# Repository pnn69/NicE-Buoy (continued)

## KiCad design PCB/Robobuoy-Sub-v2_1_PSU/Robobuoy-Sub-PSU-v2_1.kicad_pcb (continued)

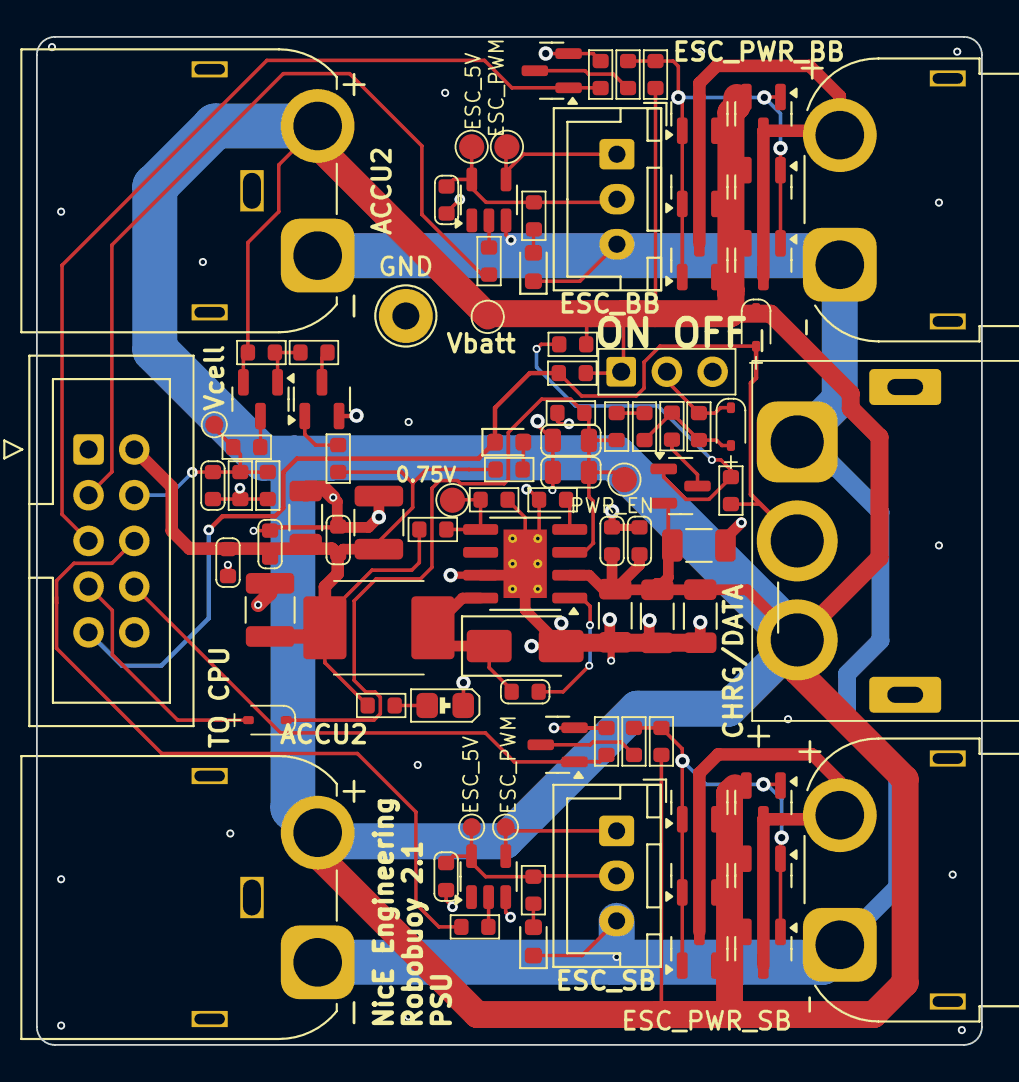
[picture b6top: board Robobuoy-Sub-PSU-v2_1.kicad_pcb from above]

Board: 4 copper layers, 52.5 x 56.0 mm, 94 parts (0 on the bottom side), 40 nets.

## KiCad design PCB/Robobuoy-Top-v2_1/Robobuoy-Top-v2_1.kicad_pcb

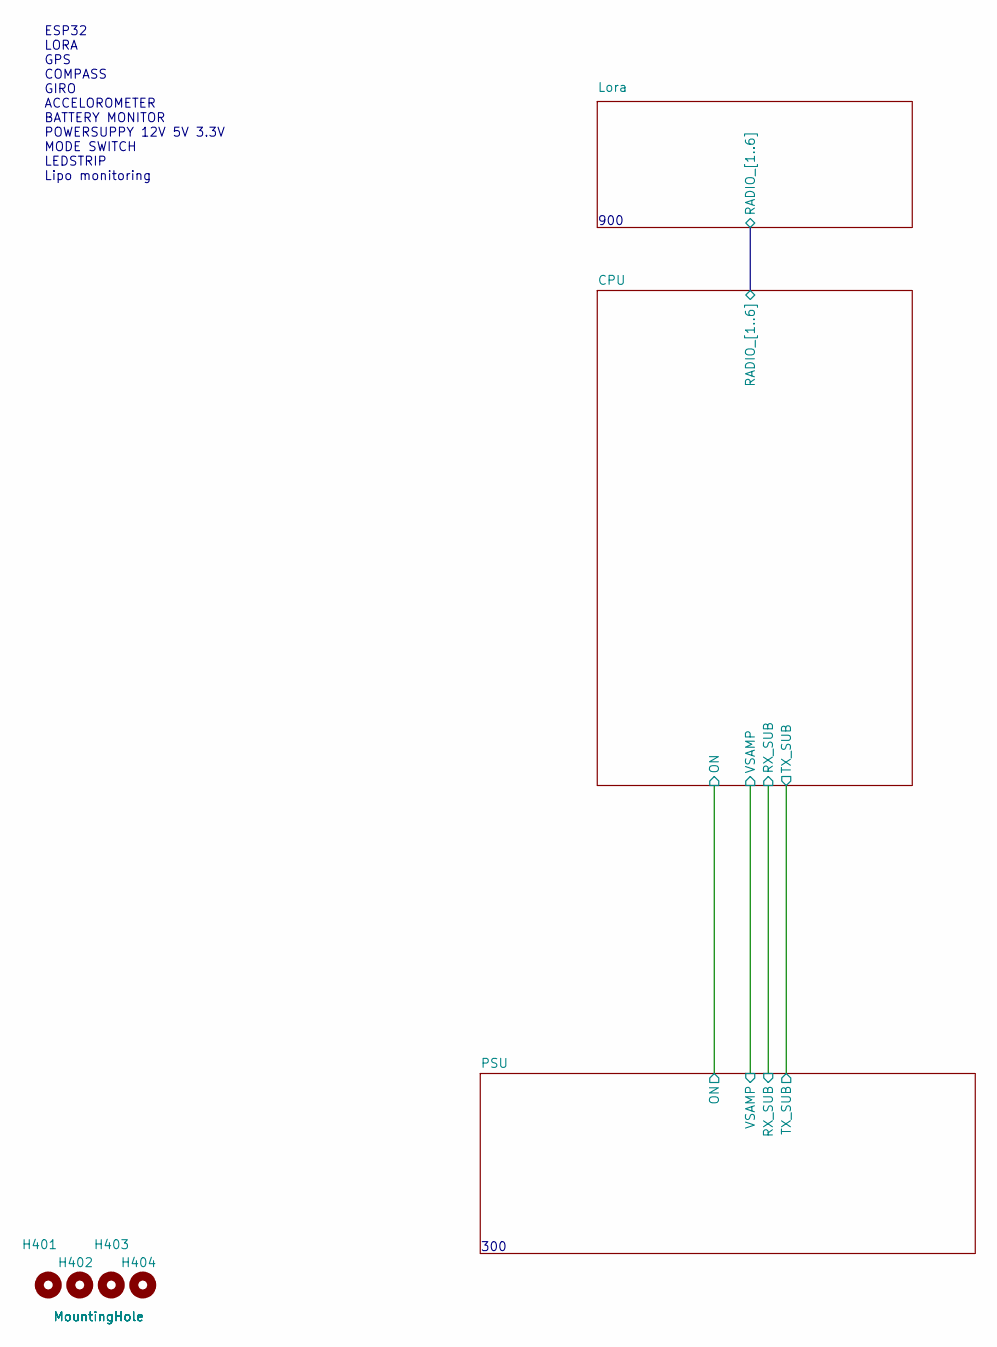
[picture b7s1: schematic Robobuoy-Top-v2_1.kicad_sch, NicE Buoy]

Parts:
H401, H402, H403, H404: MountingHole; NPTH_M3

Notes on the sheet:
300
ESP32 LORA GPS COMPASS GIRO ACCELOROMETER BATTERY MONITOR POWERSUPPY 12V 5V 3.3V MODE SWITCH LEDSTRIP Lipo monitoring
900

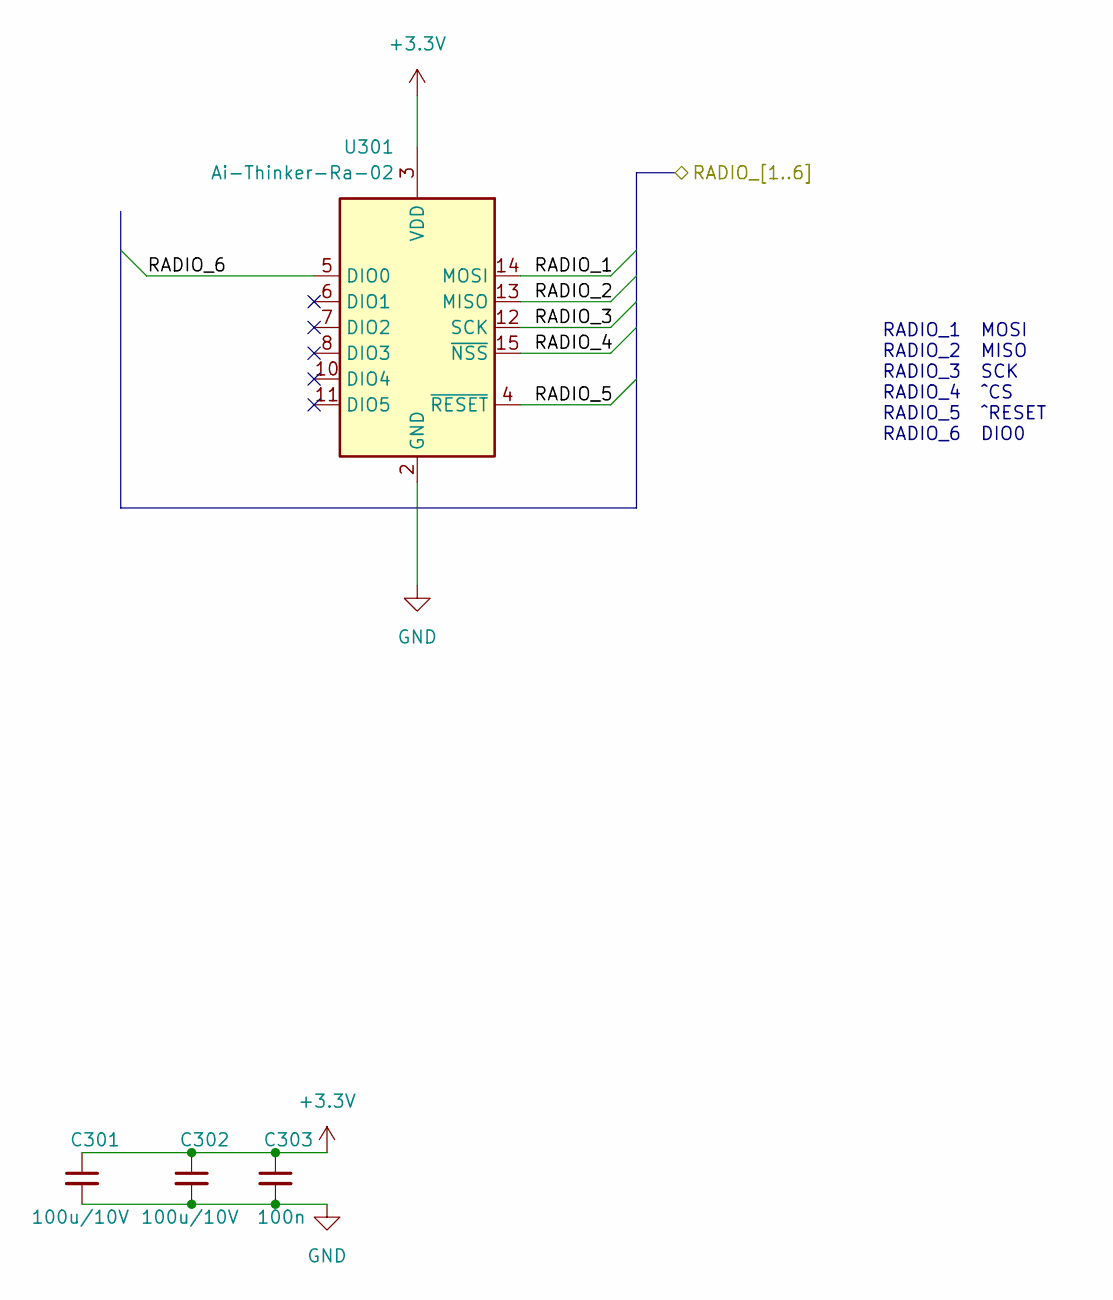
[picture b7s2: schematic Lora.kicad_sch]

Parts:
C301, C302: 100u/10V; C_1210_3225Metric; LCSC C23742
C303: 100n; C_0603; LCSC C14663
U301: Ai-Thinker-Ra-02; Ai-Thinker-Ra-02-LoRa; LCSC C90039

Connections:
+3.3V: C301.1, C302.1, C303.1, U301.3 (VDD); also elsewhere on the board
/CPU/RADIO_1: U301.14 (MOSI); also elsewhere on the board
/CPU/RADIO_2: U301.13 (MISO); also elsewhere on the board
/CPU/RADIO_3: U301.12 (SCK); also elsewhere on the board
/CPU/RADIO_4: U301.15 (~NSS); also elsewhere on the board
/CPU/RADIO_5: U301.4 (~RESET); also elsewhere on the board
/CPU/RADIO_6: U301.5 (DIO0); also elsewhere on the board
GND: C301.2, C302.2, C303.2, U301.1 (GND), U301.2 (GND), U301.9 (GND), U301.16 (GND); also elsewhere on the board

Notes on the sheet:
RADIO_1 MOSI RADIO_2 MISO RADIO_3 SCK RADIO_4 ^CS RADIO_5 ^RESET RADIO_6 DIO0

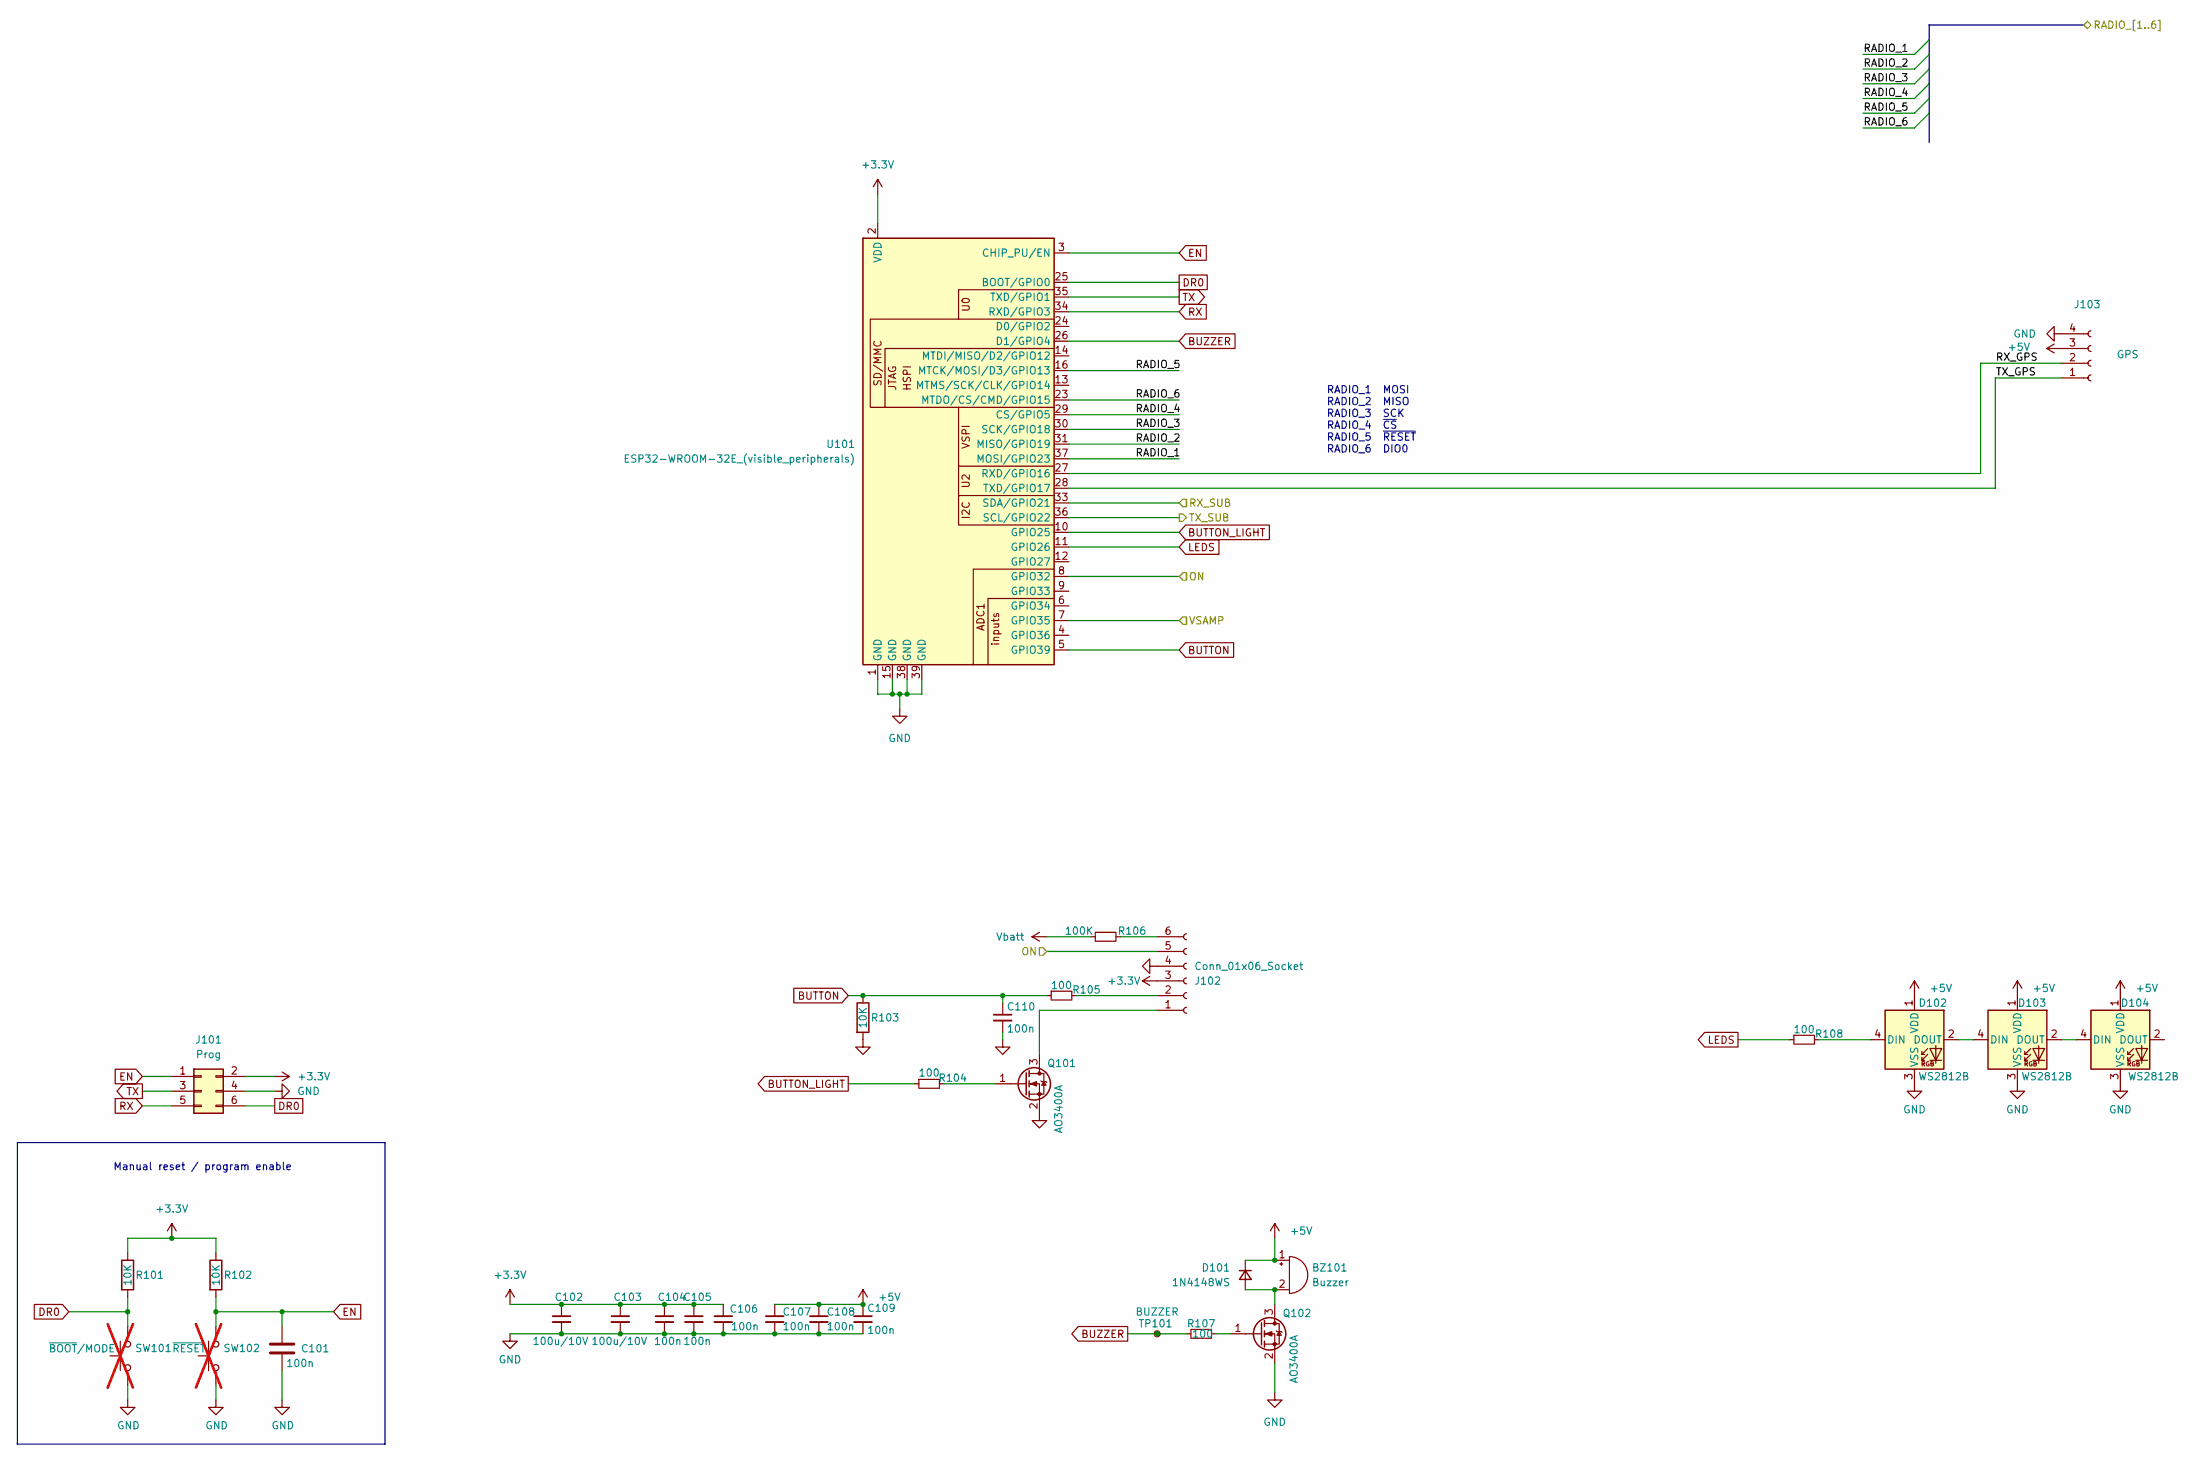
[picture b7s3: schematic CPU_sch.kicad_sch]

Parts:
BZ101: Buzzer; Buzzer-12x6.5x5.2; LCSC C968749
C101, C104, C105, C106, C107, C108, C109, C110: 100n; C_0603; LCSC C14663
C102, C103: 100u/10V; C_1210_3225Metric; LCSC C23742
D101: 1N4148WS; D_SOD-323_1.8x1.4x1.15; LCSC C2128
D102, D103, D104: WS2812B; LED_WS2812B_PLCC4_5.0x5.0mm_P3.2mm; LCSC C2843785
J101: Prog; IDC-Header_2x03_P2.54mm_Vertical; LCSC C11214
J102: Conn_01x06_Socket; JST_XH_B6B-XH-A_1x06_P2.50mm_Vertical; LCSC C5341205
J103: GPS; JST_XH_B4B-XH-A_1x04_P2.50mm_Vertical; LCSC C5341203
Q101, Q102: AO3400A; SOT-23; LCSC C20917
R101, R102, R103: 10K; R_0603; Farnell 2331736
R104, R105, R107, R108: 100; R_0603; LCSC C22775
R106: 100K; R_0603; LCSC C25804
SW101: ~{BOOT}/MODE; PinHeader_1x02_P2.54mm_Vertical; not fitted
SW102: ~{RESET}; PinHeader_1x02_P2.54mm_Vertical; not fitted
TP101: BUZZER; Testpad_1
U101: ESP32-WROOM-32E_(visible_peripherals); ESP32-WROOM-32; LCSC C82899

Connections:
+3.3V: C102.1, C103.1, C104.1, C105.1, C106.1, J101.2, J102.3, R101.1, R102.1, U101.2 (VDD); also elsewhere on the board
+5V: BZ101.1 (+), C107.1, C108.1, C109.1, D101.1 (K), D102.1 (VDD), D103.1 (VDD), D104.1 (VDD), J103.3; also elsewhere on the board
/CPU/ON: J102.5, U101.8 (GPIO32); also elsewhere on the board
/CPU/RADIO_1: U101.37 (MOSI/GPIO23); also elsewhere on the board
/CPU/RADIO_2: U101.31 (MISO/GPIO19); also elsewhere on the board
/CPU/RADIO_3: U101.30 (SCK/GPIO18); also elsewhere on the board
/CPU/RADIO_4: U101.29 (CS/GPIO5); also elsewhere on the board
/CPU/RADIO_5: U101.16 (MTCK/MOSI/D3/GPIO13); also elsewhere on the board
/CPU/RADIO_6: U101.23 (MTDO/CS/CMD/GPIO15); also elsewhere on the board
/CPU/RX_GPS: J103.2, U101.27 (RXD/GPIO16)
/CPU/RX_SUB: U101.33 (SDA/GPIO21); also elsewhere on the board
/CPU/TX_GPS: J103.1, U101.28 (TXD/GPIO17)
/CPU/TX_SUB: U101.36 (SCL/GPIO22); also elsewhere on the board
/CPU/VSAMP: U101.7 (GPIO35); also elsewhere on the board
BUTTON: C110.1, R103.1, R105.1, U101.5 (GPIO39)
BUTTON_LIGHT: R104.1, U101.10 (GPIO25)
BUZZER: R107.2, TP101.1, U101.26 (D1/GPIO4)
DR0: J101.6, R101.2, SW101.2, U101.25 (BOOT/GPIO0)
EN: C101.1, J101.1, R102.2, SW102.2, U101.3 (CHIP_PU/EN)
GND: C101.2, C102.2, C103.2, C104.2, C105.2, C106.2, C107.2, C108.2, C109.2, C110.2, D102.3 (VSS), D103.3 (VSS), D104.3 (VSS), J101.4, J102.4, J103.4, Q101.2 (S), Q102.2 (S), R103.2, SW101.1, SW102.1, U101.1 (GND), U101.15 (GND), U101.38 (GND), U101.39 (GND); also elsewhere on the board
LEDS: R108.1, U101.11 (GPIO26)
unnamed: BZ101.2 (-), D101.2 (A), Q102.3 (D)
unnamed: D102.4 (DIN), R108.2
unnamed: D102.2 (DOUT), D103.4 (DIN)
unnamed: D103.2 (DOUT), D104.4 (DIN)
unnamed: J102.1, Q101.3 (D)
unnamed: J102.2, R105.2
unnamed: J102.6, R106.2
unnamed: Q101.1 (G), R104.2
unnamed: Q102.1 (G), R107.1
RX: J101.5, U101.34 (RXD/GPIO3)
TX: J101.3, U101.35 (TXD/GPIO1)
Vbatt: R106.1; also elsewhere on the board

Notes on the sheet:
RADIO_1 MOSI RADIO_2 MISO RADIO_3 SCK RADIO_4 ~{CS} RADIO_5 ~{RESET} RADIO_6 DIO0
Manual reset / program enable

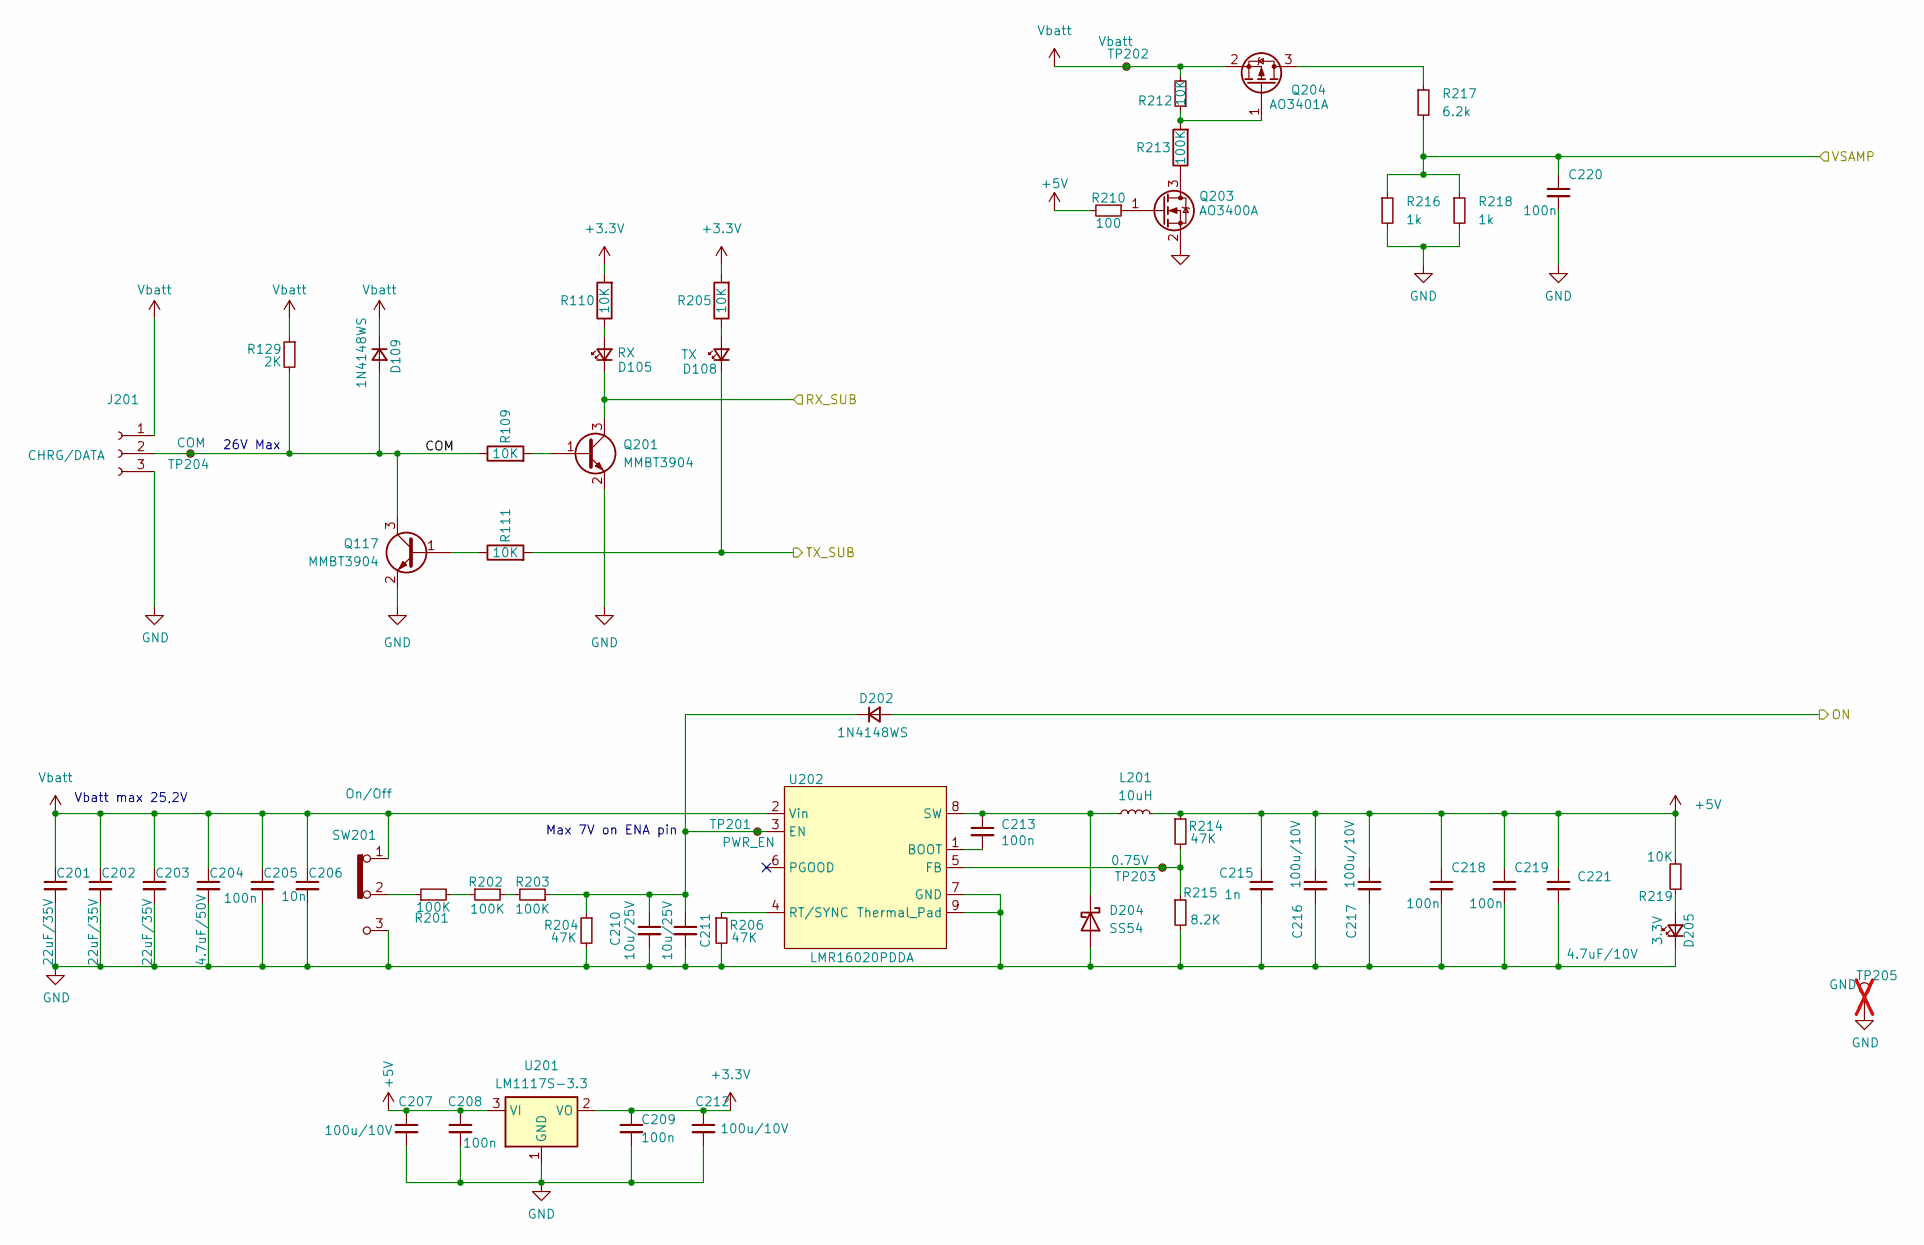
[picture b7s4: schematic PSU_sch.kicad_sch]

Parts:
C201, C202, C203: 22uF/35V; C_1206_3216Metric; LCSC C6119969
C204: 4.7uF/50V; C_1206_3216Metric; LCSC C29823
C205, C208, C209, C213, C218, C219, C220: 100n; C_0603; LCSC C14663
C206: 10n; C_0603; LCSC C57112
C207, C212, C216, C217: 100u/10V; C_1210_3225Metric; LCSC C23742
C210, C211: 10u/25V; C_0805; LCSC C15850
C215: 1n; C_0603; LCSC C1588
C221: 4.7uF/10V; C_1206_(1.6); LCSC C29823
D105: RX; LED_0805; LCSC C2297
D108: TX; LED_0805; LCSC C2297
D109, D202: 1N4148WS; D_SOD-323_1.8x1.4x1.15; LCSC C2128
D204: SS54; D_SMA; LCSC C22452
D205: 3.3V; LED_0805; LCSC C2297
J201: CHRG/DATA; JST_XH_B3B-XH-A_1x03_P2.50mm_Vertical; LCSC C5341202
L201: 10uH; L_6.6x7.0mm; LCSC C2894722
Q117, Q201: MMBT3904; SOT-23
Q203: AO3400A; SOT-23; LCSC C20917
Q204: AO3401A; SOT-23; LCSC C15127
R109, R110, R111, R205: 10K; R_0603; Farnell 2331736
R129: 2K; R_0603; LCSC C22975
R201, R202, R203: 100K; R_0603; LCSC C25804
R204, R214: 47K; R_0603
R206: 47K; R_0603; LCSC C25819
R210: 100; R_0603; LCSC C22775
R212, R219: 10K; R_0603; LCSC C25804
R213: 100K; R_0603; Farnell 2331736
R215: 8.2K; R_0603
R216, R218: 1k; R_0603; LCSC C21190
R217: 6.2k; R_0603; LCSC C25804
SW201: On/Off; Header_1x03_P2.54_Male; LCSC C2937625
TP201: PWR_EN; Testpad_1.4
TP202: Vbatt; Testpad_1.4
TP203: 0.75V; Testpad_1.4
TP204: COM; Testpad_1.4
TP205: GND; TestPoint_Loop_D2.54mm_Drill1.5mm_Beaded; not fitted
U201: LM1117S-3.3; SOT223; LCSC C126027
U202: LMR16020PDDA; SOIC-8-1EP_3.9x4.9mm_P1.27mm_EP2.41x3.81mm_ThermalVias; LCSC C190006

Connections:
+3.3V: C209.1, C212.1, R110.2, R205.2, U201.2 (VO); also elsewhere on the board
+5V: C207.1, C208.1, C215.1, C216.1, C217.1, C218.1, C219.1, C221.1, L201.2, R210.2, R214.1, R219.2, U201.3 (VI); also elsewhere on the board
/CPU/ON: D202.2 (A); also elsewhere on the board
/CPU/RX_SUB: D105.1 (K), Q201.3 (C); also elsewhere on the board
/CPU/TX_SUB: D108.1 (K), R111.2; also elsewhere on the board
/CPU/VSAMP: C220.1, R216.1, R217.2, R218.1; also elsewhere on the board
/PSU/COM: D109.2 (A), J201.2, Q117.3 (C), R109.1, R129.2, TP204.1
GND: C201.2, C202.2, C203.2, C204.2, C205.2, C206.2, C207.2, C208.2, C209.2, C210.2, C211.2, C212.2, C215.2, C216.2, C217.2, C218.2, C219.2, C220.2, C221.2, D204.2 (A), D205.1 (K), J201.3, Q117.2 (E), Q201.2 (E), Q203.2 (S), R204.2, R206.2, R215.2, R216.2, R218.2, SW201.3, TP205.1, U201.1 (GND), U202.7 (GND), U202.9 (Thermal_Pad); also elsewhere on the board
unnamed: D105.2 (A), R110.1
unnamed: D108.2 (A), R205.1
unnamed: C210.1, C211.1, D202.1 (K), R203.1, R204.1, TP201.1, U202.3 (EN)
unnamed: C213.1, D204.1 (K), L201.1, U202.8 (SW)
unnamed: D205.2 (A), R219.1
unnamed: Q117.1 (B), R111.1
unnamed: Q201.1 (B), R109.2
unnamed: Q203.3 (D), R213.1
unnamed: Q203.1 (G), R210.1
unnamed: Q204.3 (D), R217.1
unnamed: Q204.1 (G), R212.1, R213.2
unnamed: R201.1, SW201.2
unnamed: R201.2, R202.1
unnamed: R202.2, R203.2
unnamed: C213.2, U202.1 (BOOT)
unnamed: R214.2, R215.1, TP203.1, U202.5 (FB)
unnamed: R206.1, U202.4 (RT/SYNC)
Vbatt: C201.1, C202.1, C203.1, C204.1, C205.1, C206.1, D109.1 (K), J201.1, Q204.2 (S), R129.1, R212.2, SW201.1, TP202.1, U202.2 (Vin); also elsewhere on the board

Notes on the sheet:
Max 7V on ENA pin
Vbatt max 25,2V
26V Max

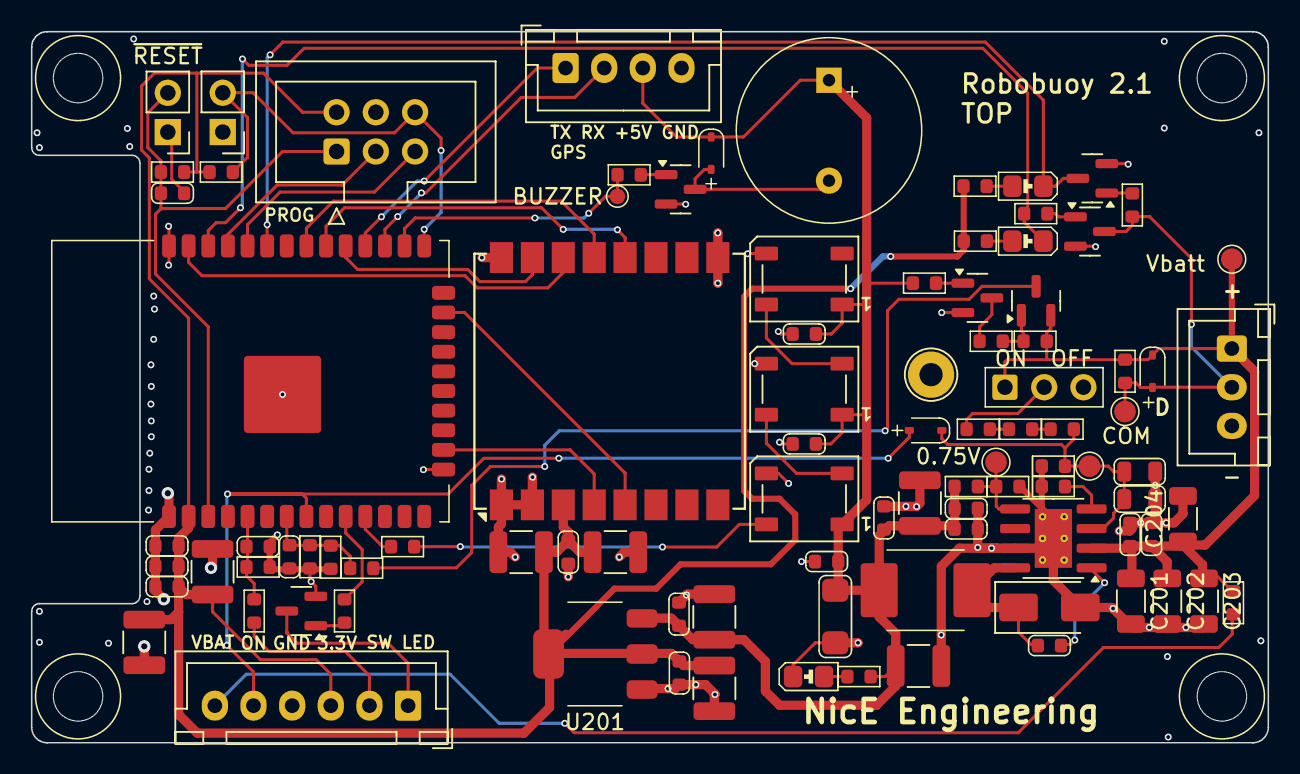
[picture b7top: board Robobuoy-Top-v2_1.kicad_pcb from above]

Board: 4 copper layers, 80.0 x 46.0 mm, 99 parts (0 on the bottom side), 51 nets.

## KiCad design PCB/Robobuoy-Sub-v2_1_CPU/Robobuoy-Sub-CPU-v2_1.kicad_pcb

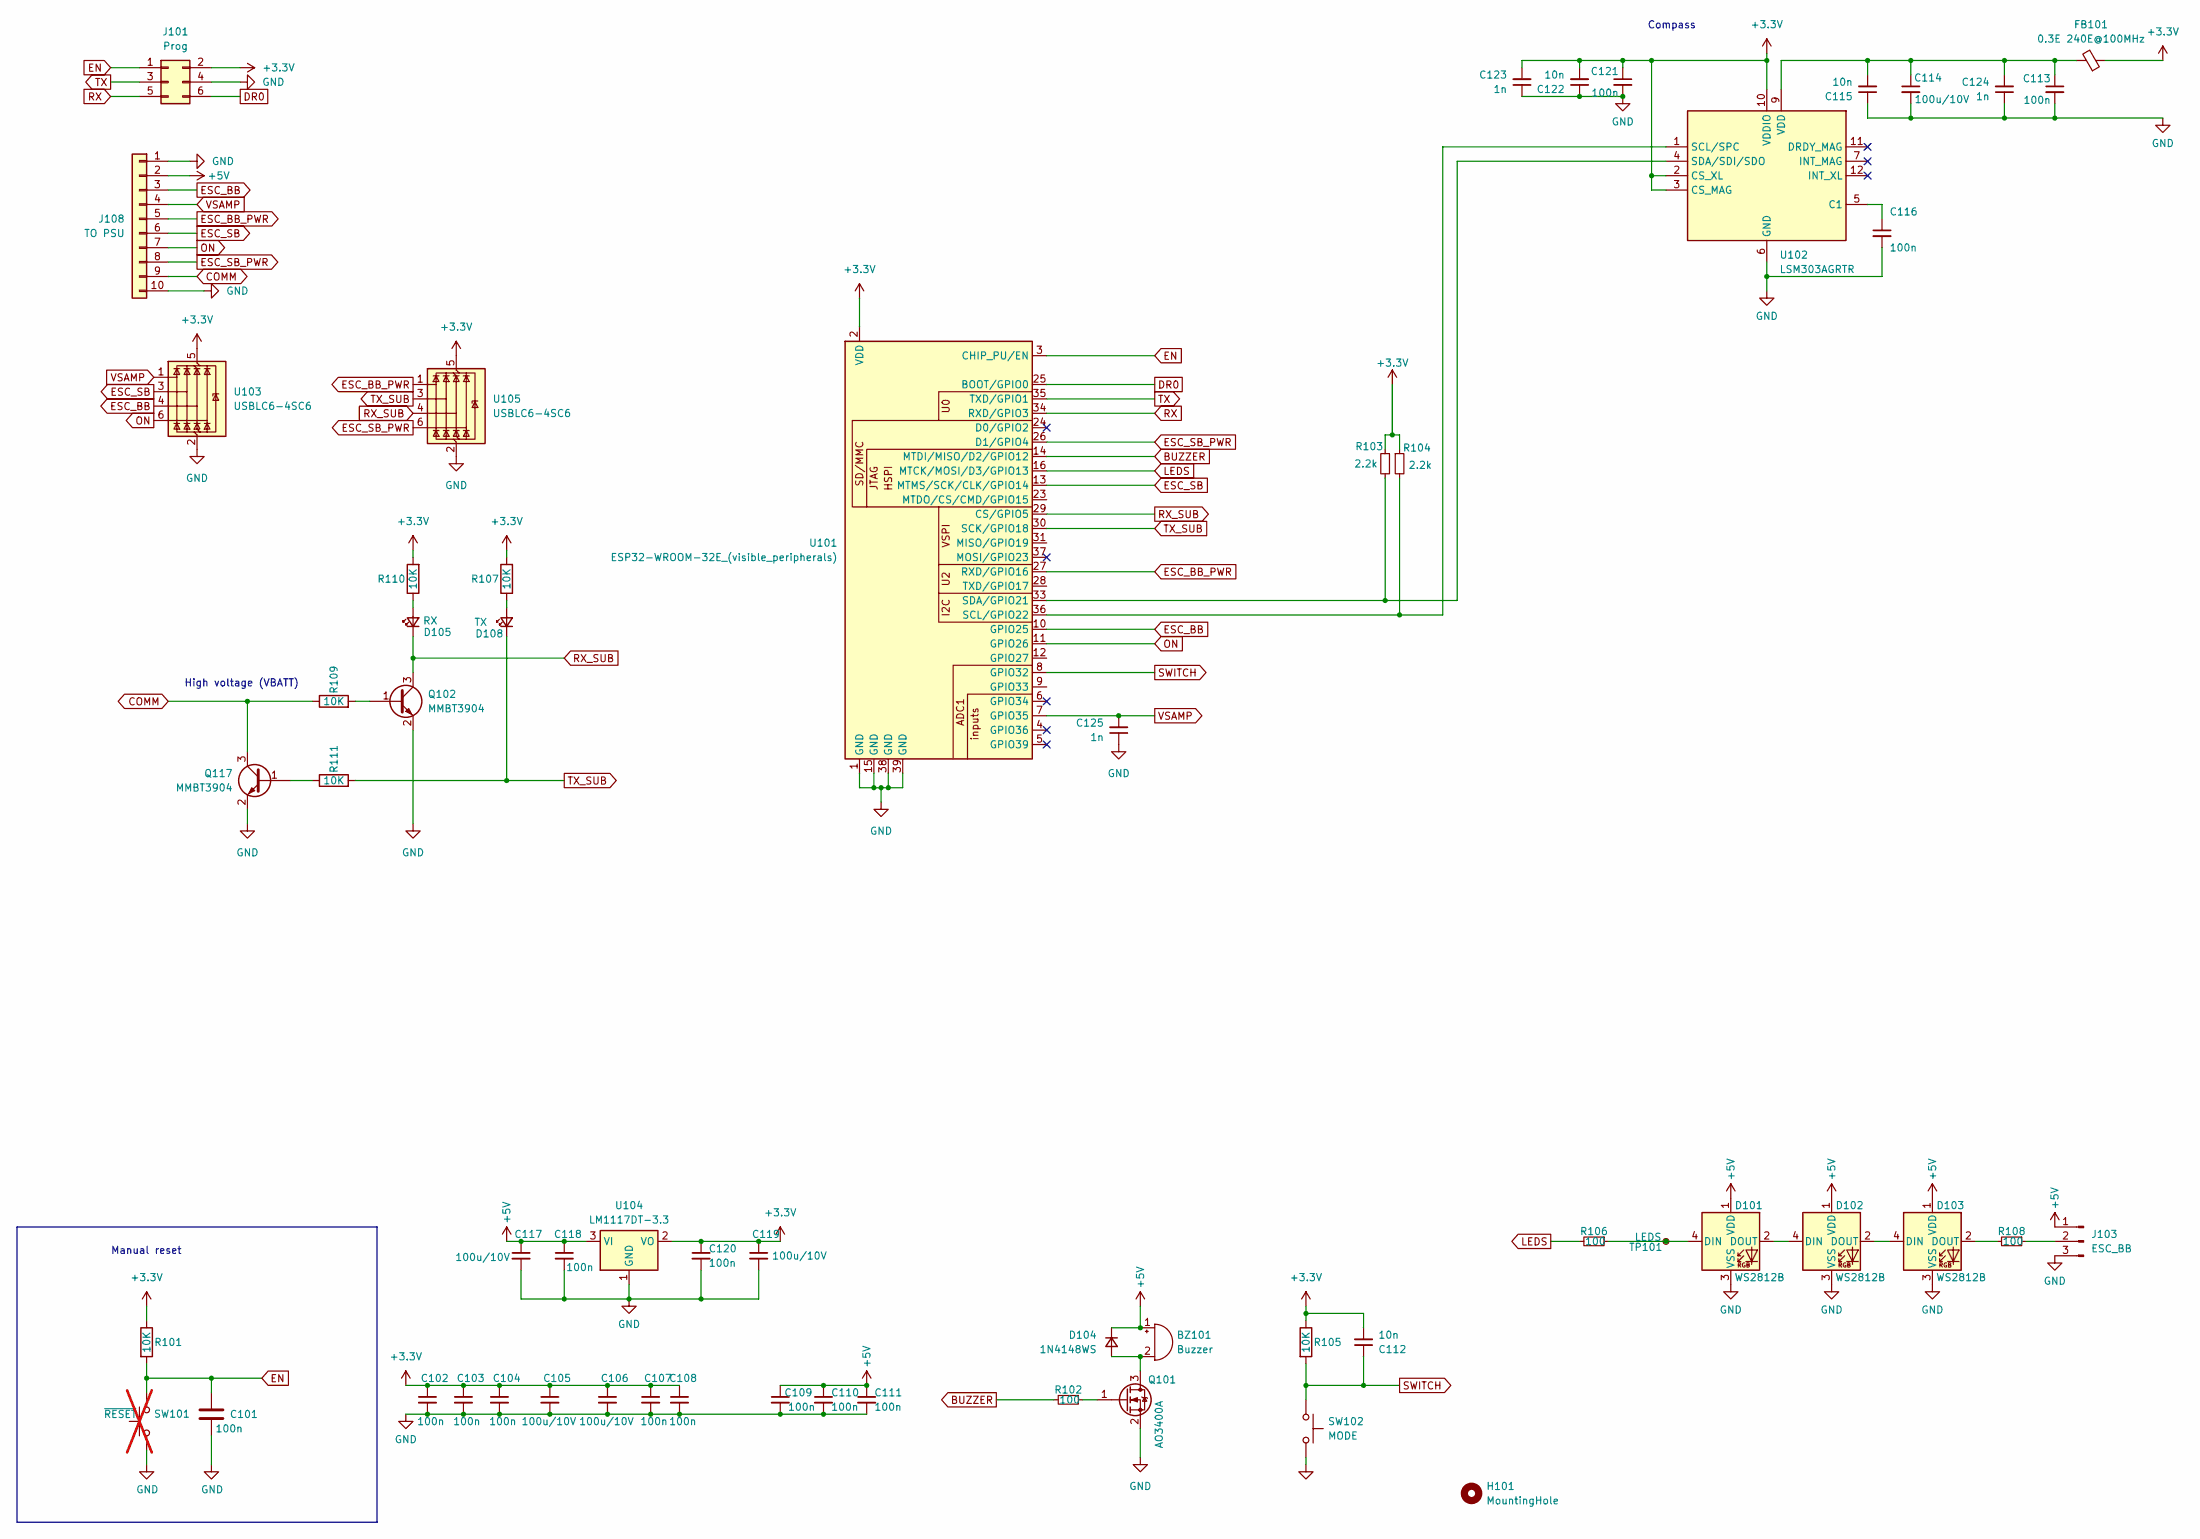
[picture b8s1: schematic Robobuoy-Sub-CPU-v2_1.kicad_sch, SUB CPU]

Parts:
BZ101: Buzzer; Buzzer-12x6.5x5.2; LCSC C968749
C101, C102, C103, C104, C107, C108, C109, C110, C111, C113, C116, C118, C120, C121: 100n; C_0603; LCSC C14663
C105, C106, C114, C117, C119: 100u/10V; C_1210_3225Metric; LCSC C23742
C112, C115, C122: 10n; C_0603; LCSC C57112
C123, C124, C125: 1n; C_0603; LCSC C1588
D101, D102, D103: WS2812B; LED_WS2812B_PLCC4_5.0x5.0mm_P3.2mm; LCSC C2843785
D104: 1N4148WS; D_SOD-323_1.8x1.4x1.15; LCSC C2128
D105: RX; LED_0805; LCSC C2297
D108: TX; LED_0805; LCSC C2297
FB101: 0.3E 240E@100MHz; L_0805_(1.2); LCSC C2941558
H101: MountingHole; MountingHole_3.2mm_M3
J101: Prog; IDC-Header_2x03_P2.54mm_Vertical; LCSC C65114
J103: ESC_BB; JST_XH_B3B-XH-A_1x03_P2.50mm_Vertical; LCSC C5341202
J108: TO PSU; IDC-Header_2x05_P2.54mm_Vertical; LCSC C5665
Q101: AO3400A; SOT-23; LCSC C20917
Q102, Q117: MMBT3904; SOT-23
R101, R105, R107, R109, R110, R111: 10K; R_0603; Farnell 2331736
R102, R106, R108: 100; R_0603; LCSC C22775
R103, R104: 2.2k; R_0603; LCSC C4190
SW101: ~{RESET}; PinHeader_1x02_P2.54mm_Vertical; not fitted
SW102: MODE; SW_SPST_TL3342; LCSC C318884
TP101: LEDS; Testpad_1
U101: ESP32-WROOM-32E_(visible_peripherals); ESP32-WROOM-32; LCSC C82899
U102: LSM303AGRTR; LGA-12_2x2mm_P0.5mm; LCSC C126671
U103, U105: USBLC6-4SC6; SOT-23-6; LCSC C5197386
U104: LM1117DT-3.3; TO-252-3_TabPin2

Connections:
+3.3V: C102.1, C103.1, C104.1, C105.1, C106.1, C107.1, C108.1, C112.2, C119.1, C120.1, C121.1, C122.2, C123.2, FB101.1, J101.2, R101.1, R103.1, R104.1, R105.1, R107.2, R110.2, U101.2 (VDD), U102.2 (CS_XL), U102.3 (CS_MAG), U102.10 (VDDIO), U103.5 (VBUS), U104.2 (VO), U105.5 (VBUS)
+5V: BZ101.1 (+), C109.1, C110.1, C111.1, C117.1, C118.1, D101.1 (VDD), D102.1 (VDD), D103.1 (VDD), D104.1 (K), J103.1, J108.2, U104.3 (VI)
BUZZER: R102.2, U101.14 (MTDI/MISO/D2/GPIO12)
COMM: J108.9, Q117.3 (C), R109.1
DR0: J101.6, U101.25 (BOOT/GPIO0)
EN: C101.1, J101.1, R101.2, SW101.2, U101.3 (CHIP_PU/EN)
ESC_BB: J108.3, U101.10 (GPIO25), U103.4 (I/O3)
ESC_BB_PWR: J108.5, U101.27 (RXD/GPIO16), U105.1 (I/O1)
ESC_SB: J108.6, U101.13 (MTMS/SCK/CLK/GPIO14), U103.3 (I/O2)
ESC_SB_PWR: J108.8, U101.26 (D1/GPIO4), U105.6 (I/O4)
GND: C101.2, C102.2, C103.2, C104.2, C105.2, C106.2, C107.2, C108.2, C109.2, C110.2, C111.2, C113.2, C114.2, C115.1, C116.2, C117.2, C118.2, C119.2, C120.2, C121.2, C122.1, C123.1, C124.1, C125.1, D101.3 (VSS), D102.3 (VSS), D103.3 (VSS), J101.4, J103.3, J108.1, J108.10, Q101.2 (S), Q102.2 (E), Q117.2 (E), SW101.1, SW102.1, U101.1 (GND), U101.15 (GND), U101.38 (GND), U101.39 (GND), U102.6 (GND), U102.8 (GND), U103.2 (GND), U104.1 (GND), U105.2 (GND)
LEDS: R106.2, U101.16 (MTCK/MOSI/D3/GPIO13)
unnamed: BZ101.2 (-), D104.2 (A), Q101.3 (D)
unnamed: D101.4 (DIN), R106.1, TP101.1
unnamed: D101.2 (DOUT), D102.4 (DIN)
unnamed: D102.2 (DOUT), D103.4 (DIN)
unnamed: D103.2 (DOUT), R108.2
unnamed: D105.2 (A), R110.1
unnamed: D108.2 (A), R107.1
unnamed: J103.2, R108.1
unnamed: Q101.1 (G), R102.1
unnamed: Q102.1 (B), R109.2
unnamed: Q117.1 (B), R111.1
unnamed: R104.2, U101.36 (SCL/GPIO22), U102.1 (SCL/SPC)
unnamed: R103.2, U101.33 (SDA/GPIO21), U102.4 (SDA/SDI/SDO)
unnamed: C116.1, U102.5 (C1)
unnamed: C113.1, C114.1, C115.2, C124.2, FB101.2, U102.9 (VDD)
ON: J108.7, U101.11 (GPIO26), U103.6 (I/O4)
RX: J101.5, U101.34 (RXD/GPIO3)
RX_SUB: D105.1 (K), Q102.3 (C), U101.29 (CS/GPIO5), U105.4 (I/O3)
SWITCH: C112.1, R105.2, SW102.2, U101.8 (GPIO32)
TX: J101.3, U101.35 (TXD/GPIO1)
TX_SUB: D108.1 (K), R111.2, U101.30 (SCK/GPIO18), U105.3 (I/O2)
VSAMP: C125.2, J108.4, U101.7 (GPIO35), U103.1 (I/O1)

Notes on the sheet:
Manual reset
High voltage (VBATT)
Compass

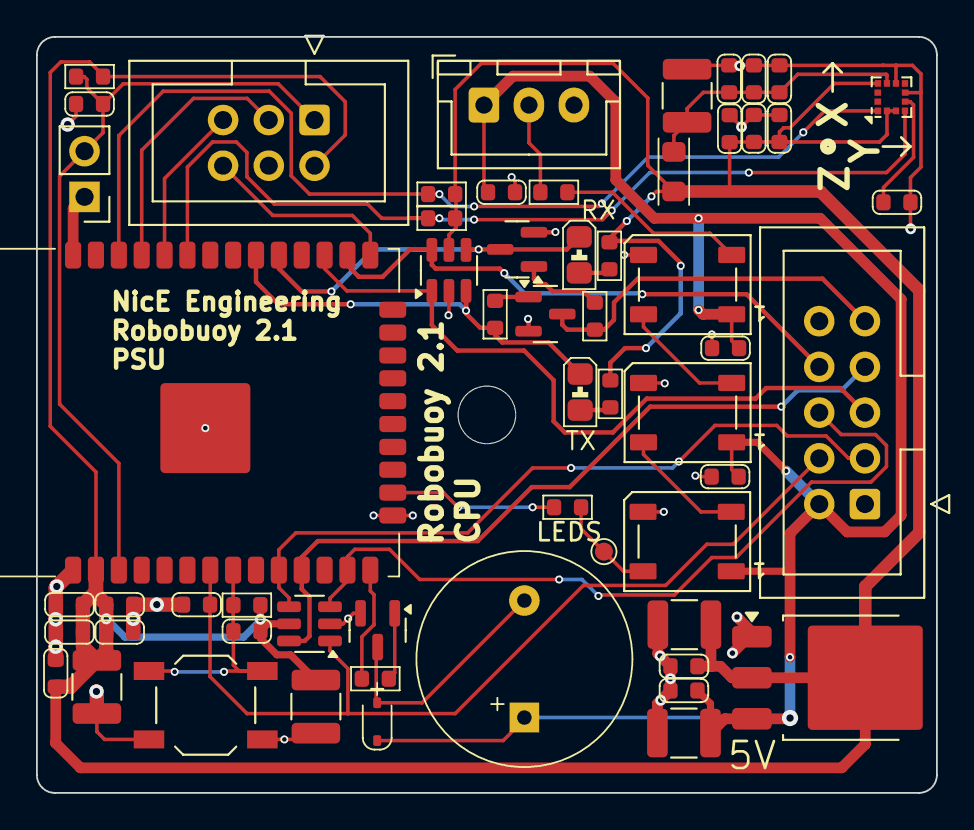
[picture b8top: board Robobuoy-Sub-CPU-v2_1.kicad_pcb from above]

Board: 4 copper layers, 50.0 x 42.0 mm, 59 parts (0 on the bottom side), 34 nets.

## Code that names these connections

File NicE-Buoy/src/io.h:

#ifndef IO_H_
#define IO_H_

#define SDA 21
#define SCL 22
#define SDA_DISP 16
#define SCL_DISP 17
#define GPSRX 33
#define GPSTX 32

#define ESC_BB_PIN 12
#define ESC_SB_PIN 14

#define VBATT 35

#define LED_PIN 25
#define LEDSTRIPPIN 26

#define SWITCH_STANDBY 36
#define SWITCH_LOCK 39
#define BAT_PIN 35

#define RADIO_SCLK_PIN 18
#define RADIO_MISO_PIN 19
#define RADIO_MOSI_PIN 23
#define RADIO_CS_PIN 5
#define RADIO_DIO0_PIN 26
#define RADIO_RST_PIN 14
#define RADIO_DIO1_PIN 12
// #define RADIO_BUSY_PIN 32

#define MCP23017_ADDR 0x20
#define SWITCH1_GPA 2
#define SWITCH2_GPA 1
#define SWITCH3_GPA 0
#define LED1_GPA 3
#define LED2_GPA 4
#define LED3_GPA 5
#define LEDYELLOW_GPA 6
#define LEDRED_GPA 7
#define MAINSSWITCH_LEDGREEN_GPB 8
#define MAINSSWITCH_LEDRED_GPB 9
#define SWITCHV3V3_GPB 10
#define SWITCHPWRVBATT_GPB 11
#define SWITCH_T1_GPB 12
#define SWITCH_T2_GPB 13

#define LoRa_frequency 433E6

// switch
#define SWITCH1 36
#define SWITCH2 39

#define BUZZERPIN 13
#endif /* IO_H_ */

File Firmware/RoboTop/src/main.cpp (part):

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    myPID.SetOutputLimits(-100, 100);

    pinMode(BUTTON_PIN, INPUT);
    pinMode(BUZZER_PIN, OUTPUT);
    pinMode(BUTTON_LIGHT_PIN, OUTPUT);
    delay(100);
    printf("\r\n\r\nRobobuoy Top Version: %0.1f\r\n", TOPVERSION);
    printf("Build Date: %s %s\r\n", __DATE__, __TIME__);
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        buttonBlinkTimer = millis() + blink;
        if (sta->status == LOCKED || sta->status == DOCKED)
        {
            digitalWrite(BUTTON_LIGHT_PIN, HIGH);
            blink = 2000;
        }
        else if (sta->status == CALIBRATE_MAGNETIC_COMPASS)
        {
            digitalWrite(BUTTON_LIGHT_PIN, !digitalRead(BUTTON_LIGHT_PIN));
            blink = 50;
        }
        else
        {
            digitalWrite(BUTTON_LIGHT_PIN, !digitalRead(BUTTON_LIGHT_PIN));
            if (sta->gpsFix == true)
            {
                if (blink != 1000)
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        //
        // Over LoRa this never mattered: onReceive() consumes an ACK addressed to us and returns,
        // so it does not reach this function at all. Over UDP there is no such filter - the frame
        // arrives through udpIn like any other - and the switch below dispatches on RfIn.cmd. An
        // ACK for SETLOCKPOS would therefore be run AS a SETLOCKPOS, and RoboCode() emits only
        // "cmd,status" for an ACK, so its tgLat/tgLng decode as 0,0: the buoy that had just
        // computed the start line would answer its peer's receipt by setting its own waypoint to
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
